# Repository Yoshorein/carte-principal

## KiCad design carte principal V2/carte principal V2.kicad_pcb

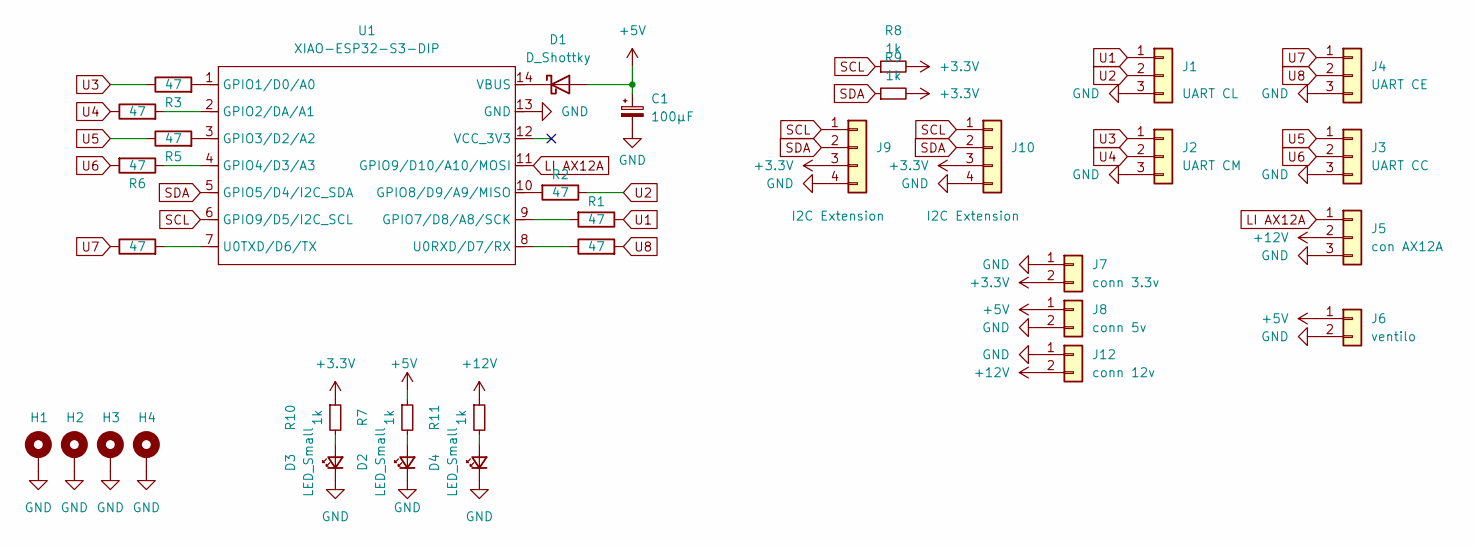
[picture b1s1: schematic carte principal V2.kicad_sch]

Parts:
C1: 100µF; CP_Radial_D5.0mm_P2.00mm
D1: D_Shottky; D_DO-41_SOD81_P10.16mm_Horizontal
D2, D3, D4: LED_Small; LED_1206_3216Metric
H1, H2, H3, H4: MountingHole_Pad; MountingHole_3.2mm_M3_Pad_Via
J1: UART CL; Molex_KK-254_AE-6410-03A_1x03_P2.54mm_Vertical
J2: UART CM; Molex_KK-254_AE-6410-03A_1x03_P2.54mm_Vertical
J3: UART CC; Molex_KK-254_AE-6410-03A_1x03_P2.54mm_Vertical
J4: UART CE; Molex_KK-254_AE-6410-03A_1x03_P2.54mm_Vertical
J5: con AX12A; Molex_KK-254_AE-6410-03A_1x03_P2.54mm_Vertical
J6: ventilo; Molex_KK-254_AE-6410-02A_1x02_P2.54mm_Vertical
J7: conn 3.3v; AMASS_XT30U-F_1x02_P5.0mm_Vertical
J8: conn 5v; Molex_KK-254_AE-6410-02A_1x02_P2.54mm_Vertical
J9, J10: I2C Extension; Molex_KK-254_AE-6410-04A_1x04_P2.54mm_Vertical
J12: conn 12v; AMASS_XT30U-F_1x02_P5.0mm_Vertical
R1, R2, R3, R4, R5, R6, R12, R13: 47; R_1206_3216Metric_Pad1.30x1.75mm_HandSolder
R7, R8, R9, R10, R11: 1k; R_1206_3216Metric_Pad1.30x1.75mm_HandSolder
U1: XIAO-ESP32-S3-DIP; XIAO-ESP32S3-DIP

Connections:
+3.3V: J7.2, J9.3, J10.3, R8.2, R9.2, R10.1
+5V: C1.1, D1.2 (A), J6.1, J8.1, R7.1
+12V: J5.2, J12.2, R11.1
GND: C1.2, D2.1 (K), D3.1 (K), D4.1 (K), H1.1, H2.1, H3.1, H4.1, J1.3, J2.3, J3.3, J4.3, J5.3, J6.2, J7.1, J8.2, J9.4, J10.4, J12.1, U1.13 (GND)
LI AX12A: J5.1, U1.11 (GPIO9/D10/A10/MOSI)
unnamed: D1.1 (K), U1.14 (VBUS)
unnamed: D2.2 (A), R7.2
unnamed: D3.2 (A), R10.2
unnamed: D4.2 (A), R11.2
unnamed: R3.2, U1.1 (GPIO1/D0/A0)
unnamed: R4.2, U1.2 (GPIO2/DA/A1)
unnamed: R5.2, U1.3 (GPIO3/D2/A2)
unnamed: R6.1, U1.4 (GPIO4/D3/A3)
unnamed: R1.2, U1.9 (GPIO7/D8/A8/SCK)
unnamed: R2.2, U1.10 (GPIO8/D9/A9/MISO)
unnamed: R12.1, U1.8 (U0RXD/D7/RX)
unnamed: R13.2, U1.7 (U0TXD/D6/TX)
SCL: J9.1, J10.1, R8.1, U1.6 (GPIO9/D5/I2C_SCL)
SDA: J9.2, J10.2, R9.1, U1.5 (GPIO5/D4/I2C_SDA)
U1: J1.1, R1.1
U2: J1.2, R2.1
U3: J2.1, R3.1
U4: J2.2, R4.1
U5: J3.1, R5.1
U6: J3.2, R6.2
U7: J4.1, R13.1
U8: J4.2, R12.2

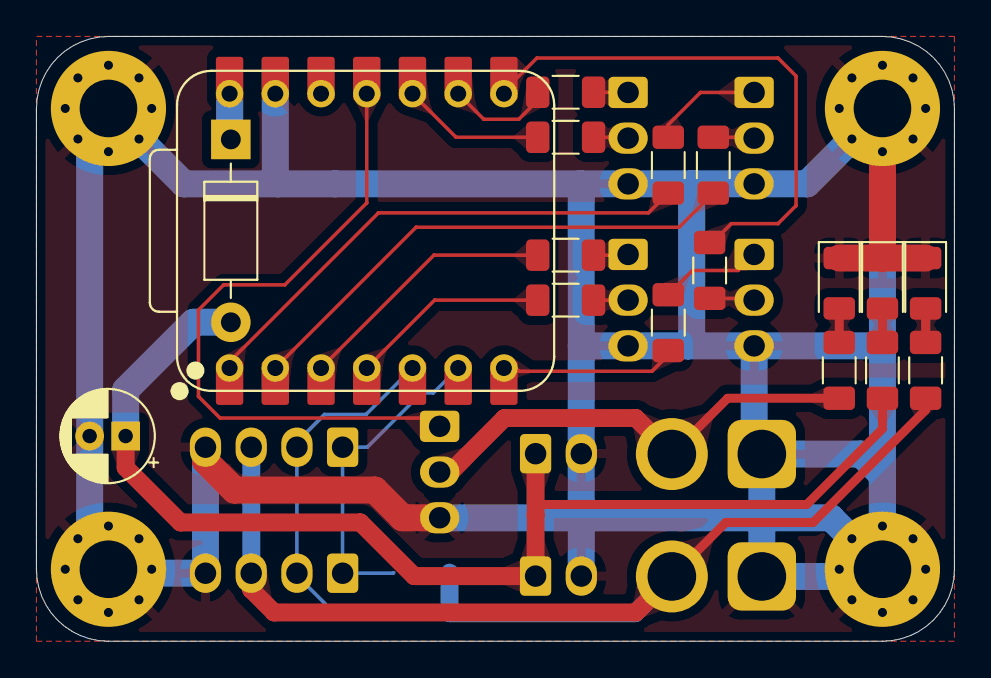
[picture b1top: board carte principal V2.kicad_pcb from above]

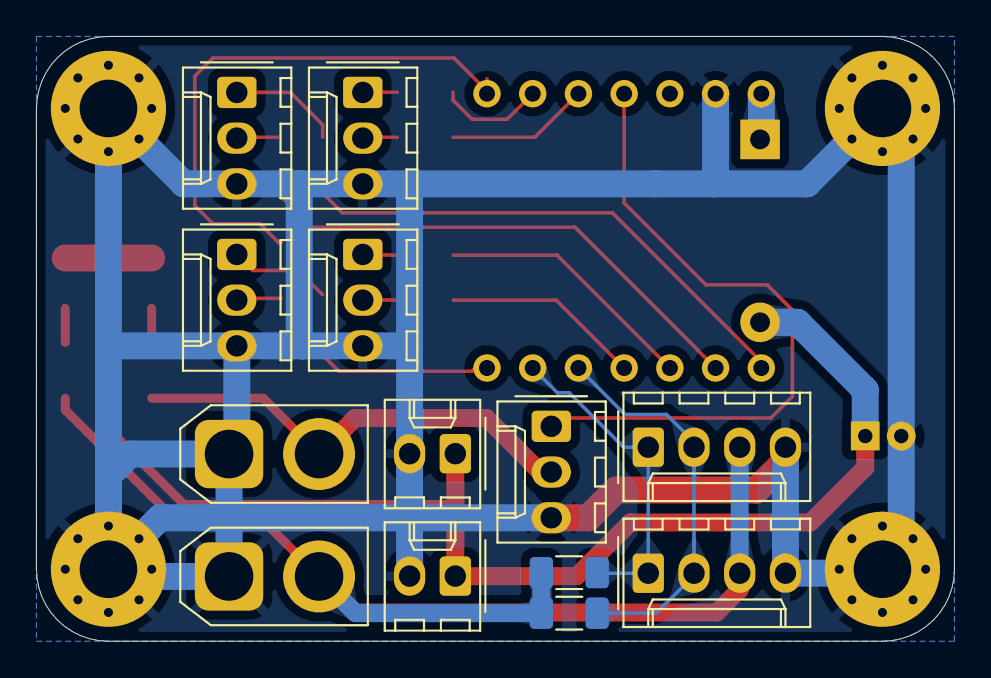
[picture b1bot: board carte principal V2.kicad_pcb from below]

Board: 2 copper layers, 51.0 x 33.6 mm, 34 parts (13 on the bottom side), 27 nets.

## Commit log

2025-10-21 first routage
2025-11-03 apdavph
2025-11-05 là aussi
2025-11-12 des ptit fixes
